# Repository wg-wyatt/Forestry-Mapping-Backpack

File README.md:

# Forestry Mapping Backpack

<table align="center" width="100%">
  <tr>
    <td align="center" valign="middle" width="50%">
      
      <br>
      <b>Exterior Assembly</b>
    </td>
    <td align="center" valign="middle" width="50%">
      
      <br>
      <b>Interior Assembly</b>
    </td>
  </tr>
</table>

---

## Overview
The LiDAR Backpack Mapping System is a mobile, human-wearable sensing platform engineered to improve 3D point cloud density and spatial coverage for forestry and ecological surveying. Developed to replace rigid mast-mounted sensors, the system integrates a continuous secondary rotation axis with onboard processing to optimize sensor range, lower the user's center of gravity, and improve ergonomics during extended field deployment.

---

## Key Features

- Rotating LiDAR platform
- Integrated IMU for spatial orientation
- Modular mechanical architecture
- MATLAB analysis supporting point cloud generation
- Timing belt-driven rotation system
- Custom KiCad PCB
- FEA-validated structural design
- Optimized for low-volume manufacturing

### Project Disclaimer

This project was completed in collaboration with the Purdue Forestry Department. Certain project details, files, and implementation documentation may be limited due to sponsor requirements and intellectual property considerations.

---

## Problem Statement
The Purdue Forestry Department utilizes a machine learning–based plant recognition system to assist researchers with ecological surveying and vegetation analysis. Their legacy setup relied on a static LiDAR sensor mounted atop a tall backpack support mast. This configuration suffered from two major limitations:
* **Limited Spatial Coverage:** The static sensor depended entirely on natural user motion during field traversal to expand scan coverage, leading to low point cloud density and occlusions.
* **Poor Ergonomics:** Positioning significant mass high above the backpack shifted the system's center of gravity, reducing stability and user comfort during extended hiking over uneven terrain.

The objective of this project was to engineer a field-deployable mounting platform that adds a continuous secondary rotation axis to maximize point cloud density while relocating system mass closer to the user's center of gravity.

---

## Design Requirements

The following design requirements were established during the concept development phase to guide system architecture and engineering decisions. Requirements were selected to balance field usability, sensing performance, manufacturability, and compatibility with the existing Purdue Forestry Department backpack platform.

### Mechanical Requirements

| ID | Requirement | Target | Verification Method |
|----|-------------|--------|---------------------|
| DR-01 | Total system weight | < 10 kg (excluding backpack) | CAD mass properties |
| DR-02 | Structural durability | Withstand 5 g loading without structural failure | Finite Element Analysis (FEA) |
| DR-03 | Manufacturability | Components shall be manufacturable using conventional CNC machining, sheet metal fabrication, additive manufacturing, and commercially available hardware | Design review and manufacturing drawings |
| DR-04 | Serviceability | Electronics and wearable components shall be removable without permanent modification to the assembly | Assembly review |

### Functional Requirements

| ID | Requirement | Target | Verification Method |
|----|-------------|--------|---------------------|
| FR-01 | Point cloud coverage | Provide 360° scanning with a secondary axis of rotation to improve spatial coverage and reduce occlusions | MATLAB analysis and future field validation |
| FR-02 | Rotational position tracking | Report motor position to ±0.01° for point cloud reconstruction | Encoder specification and software verification |

### Integration Requirements

| ID | Requirement | Target | Verification Method |
|----|-------------|--------|---------------------|
| IR-01 | Backpack compatibility | Integrate with the existing Purdue Forestry backpack frame, 24 V hot-swappable M18 battery system, and existing data interfaces | CAD integration and electrical design review |
| IR-02 | Environmental protection | Minimum enclosure protection equivalent to IP32 | Enclosure design review and future ingress testing |

---

## System Architecture

The LiDAR Backpack Mapping System is a modular mechatronic platform structured into four core subsystems: **Sensing**, **Motion Control**, **Power Distribution**, and **Processing & Data**. 

### Sensing System
The sensing subsystem consists of an Ouster OS1 LiDAR sensor paired with an Ellipse N inertial measurement unit (IMU). The LiDAR provides high-resolution 3D measurements, while the IMU provides time synchronization and spatial orientation. Combining these inputs with rotational position feedback enables full point-cloud reconstruction.

### Motion Control System
The motion control subsystem provides controlled rotation of the LiDAR assembly via a motor-driven mechanism. A geared timing belt transmission ensures stable torque delivery, while encoder feedback tracks rotational position to synchronize scanning motion with sensor data.

### Power Distribution System
The system utilizes a 24 V hot-swappable battery architecture inherited from the base backpack platform. Dedicated regulation hardware distributes power safely to the LiDAR, motor controller, embedded electronics, and compute unit.

### Processing and Data System
An NVIDIA Jetson Orin platform serves as the central compute unit, handling data acquisition, sensor synchronization, and point-cloud generation. Communication protocols across all hardware are streamlined to minimize external cabling and maintain reliable data transfer.

---

## Mechanical Design

<table border="0" cellpadding="10" cellspacing="0" width="100%">
  <tr>
    <td width="40%" align="center" valign="middle">
      
    </td>
    <td width="60%" valign="middle">
      <p>The mechanical architecture focuses on a modular, field-serviceable platform designed to integrate all sub-assemblies while maintaining full compatibility with the host Purdue Forestry backpack frame. The physical layout prioritizes low system mass, protected cable routing, and high structural rigidity under dynamic motion.</p>
    </td>
  </tr>
</table>

### Rotational Drive System
A motor-driven timing belt transmission provides continuous rotation for the LiDAR assembly based on velocity parameters defined in MATLAB. A compact T2 timing belt system was selected for high torque transfer and reliable engagement using off-the-shelf hardware.

The drivetrain uses a 15-tooth driving pulley and a 75-tooth driven pulley to deliver a 5:1 reduction ratio. This reduction increases output torque to provide smooth, stable rotational motion across variable operating speeds.

### Structural Packaging & Integration
The frame and enclosure assemblies are structured to support the mechanical loads of the continuous rotation drive without requiring structural overhaul of the base backpack:
* **Drive Support Frame:** Provides a rigid mounting interface for the motor, bearing stack, and pulley system to maintain precise belt alignment and tension during dynamic motion.
* **Unified Component Enclosure:** Houses the compute, power regulation, and data acquisition hardware within a single physical module, allowing for seamless electrical integration between the motion system and the original architecture
* **Serviceable Assemblies:** Component layouts allow the drive assembly or processing housing to be accessed and serviced independently without full frame disassembly.

---

## Electrical Design

The electrical architecture was designed to integrate the LiDAR sensor, IMU, motor control system, embedded controller, and onboard processing hardware into the existing Purdue Forestry backpack platform. The design focused on maintaining compatibility with the legacy 24 V power system while providing reliable communication between sensing, motion, and processing subsystems.

<p align="center">
  
  <br>
  <em>System Overview Diagram</em>
</p>

### Drive System

The purpose of the design is to provide closed-loop control of the LiDAR rotation axis while maintaining reliable communication between the motion hardware and the onboard processing system.

<p align="center">
  
  <br>
  <em>Motor Drive System Schematic</em>
</p>

The embedded controller communicates with the motor driver to provide rotational commands, including direction and speed control. The motor driver supplies the required power to the actuator while isolating the low-power control electronics from the higher-current motor circuit.

An encoder feedback system is integrated into the drive architecture to provide rotational position information. This feedback allows the system to monitor the actual motor position and provides the positional data required to synchronize the LiDAR scan with the mechanical rotation of the secondary axis.

The drive system architecture consists of:

- **Embedded controller:** Generates motion commands and manages communication with the motor driver and feedback devices.
- **Motor driver:** Converts low-power control signals into the required motor power output.
- **Motor and encoder:** Provide rotational actuation and position feedback for closed-loop monitoring.

The schematic was developed to separate power, control, and feedback signals, improving system organization and simplifying future troubleshooting, fabrication, and integration.

### PCB Design

A custom PCB was developed to consolidate system interfaces and simplify integration between the embedded controller, sensors, and external hardware. The board provides organized connections for power, communication, and control signals while reducing wiring complexity compared to a fully discrete implementation.

Future revisions would integrate additional functionality into a single consolidated interface board to further improve reliability, manufacturability, and ease of assembly.

<p align="center">
  
  <br>
  <em>Custom interface board routing and connector layout</em>
</p>

<p align="center">
  📂 <strong><a href="Electronics">View Schematic & Board Layout Files (Electronics Folder)</a></strong>
</p>

---

## System Software & Embedded Controls

The system utilizes an NVIDIA Jetson Orin Nano onboard compute module running custom proprietary software to process incoming sensor streams, generate real-time 3D point clouds, and execute plant species identification algorithms. Working in tandem with the primary compute, an embedded microcontroller manages closed-loop motor dynamics, sensor data acquisition, and precise timestamping:

* **Embedded Speed Control:** Interfaces directly with motor Hall effect sensors via the motor controller to provide closed-loop control. The motor operates at **35 Hz** to drive the geared transmission, maintaining the secondary axis LiDAR rotation at a continuous, stable **7 Hz**.
* **Encoder & IMU Data Processing:** Processes quadrature encoder data for real-time rotational position tracking while timestamping high-rate IMU telemetry to ensure precise spatial orientation and point cloud time synchronization.
* **Pipeline Processing:** Synchronizes raw LiDAR packet streams with orientation data, applying coordinate transformations and noise filtering to export uniform, high-density point cloud files (`.ply` / `.pcd`) ready for forestry canopy analysis.

📂 **[View Embedded System Firmware (Complete_Code.ino)](Analysis%20%26%20Code/Complete_Code/Complete_Code.ino)**

---

## LiDAR Coverage Analysis

Engineering analysis was used to establish design parameters and validate critical system decisions. The analysis process began by evaluating the relationship between LiDAR measurement characteristics and scanning motion, which informed the required rotational velocity of the system. Mechanical drive calculations were then performed to select an appropriate transmission design, followed by structural analysis of the final assembly.

### MATLAB Scanning Analysis
A MATLAB model was developed to simulate the point cloud generated by a LiDAR unit rotating about two independent axes. The objective of the analysis was to determine the external rotational frequency required to achieve complete and uniform point cloud coverage from a stationary position.

The LiDAR's internal emitter operates at a rotational frequency of 10 Hz. Because the LiDAR was mounted on a secondary rotating axis, the relationship between the internal scan frequency and the external rotational frequency directly influences point cloud density and spatial coverage. Selecting an external rotational frequency that is an integer factor or multiple of the internal 10 Hz scan frequency results in periodic overlap of the scan pattern, producing incomplete coverage and gaps within the reconstructed point cloud.

Multiple external rotational frequencies were evaluated using the MATLAB model. Simulation results demonstrated that secondary axis rotational frequencies of **3 Hz** and **7 Hz** produced the most uniform point cloud distribution while minimizing repeated scan paths. Based on these results, the external rotational speed requirement for the mechanical drive system was established.

<p align="center">
  
  <br>
  <em>MATLAB Simulation showing point cloud coverage density over a 360-degree sweep at a 2.0 RPM target secondary axis speed</em>
</p>

The complete simulation script used to model the scanning spatial density can be accessed here:
👉 **[LiDAR_CoverageArea.m](Analysis%20%26%20Code/LiDAR_CoverageArea.m)**

### Rotation System and Gear Design

The rotational drive system was developed to achieve the operating speed established through the MATLAB analysis while maintaining reliable torque transmission and compact packaging.

A T2 timing belt was selected to provide positive, slip-free torque transmission between the motor and the rotating LiDAR assembly. Manufacturer design recommendations from MiSUMi were used during transmission selection, including a maximum recommended reduction ratio of **5:1** and a minimum pinion tooth engagement greater than six teeth. A 2 mm pitch timing belt was selected because it is commonly used in high-precision, low-speed motion systems and is readily available as a commercial component.

Using the selected pinion gear, the driven pulley diameter, tooth count, center-to-center pulley spacing, and timing belt length were analytically determined to satisfy both the required reduction ratio and packaging constraints.

Once the drivetrain geometry was established, the rotating assembly was modeled to estimate its mass moment of inertia. The driven pulley was approximated as a solid cylinder, while the LiDAR assembly was modeled as a rotating mass about the same axis. These values were used to calculate the torque required to accelerate the system to its operating speed within the desired startup time.

The calculated rotational speed and torque requirements were compared against the selected motor specifications to verify that the drivetrain would operate within the manufacturer's recommended operating range.

<p align="center">
  📂 <strong><a href="Analysis%20%26%20Code/GearSystemCalc.pdf">View Gear System Calculations (GearSystemCalc.docx)</a></strong>
</p>

## Structural & Dynamic Analysis (FEA)

Finite element analysis (FEA) was performed to evaluate the structural integrity and dynamic response of the redesigned LiDAR backpack assembly under operational shock and vibration conditions. 

<p align="center">
  
  <br>
  <em>Full Assembly Static Stress Distribution (5 g Inertial Shock Load)</em>
</p>

### Static Structural Analysis
A uniform **5 g inertial shock acceleration** was applied to evaluate structural yield margins during field transport. Component materials were modeled as linear elastic, with sheet metal structures utilizing shell or solid elements based on section thickness. Non-structural electronics were represented as equivalent point masses to maintain accurate inertial loading while optimizing solver performance.

<div align="center">

| Assembly / Component | Max Displacement | Max Von Mises Stress | Factor of Safety (FoS) |
| :--- | :---: | :---: | :---: |
| **LiDAR Mounting Bracket** | 0.044 mm | 13.42 MPa | 20.62 |
| **Motor Bracket Assembly** | 0.048 mm | 13.00 MPa | 4.95 |
| **Full Structural Assembly** | 0.085 mm | 15.30 MPa | 4.27 |

</div>

* **Structural Integrity:** The carbon fiber backplate and aluminum mounting hardware maintain significant structural margin under 5 g shock conditions, exceeding yield safety factor requirements with a minimum assembly FoS of **4.27x**.
* **Deflection Limits:** Maximum full-assembly displacement is constrained to **0.085 mm**, maintaining precise positional stability for high-accuracy point cloud generation.

---

### Modal Frequency Analysis
Modal analysis was performed to identify assembly natural frequencies and prevent forced resonance with primary system excitation sources (LiDAR internal sweep at 10 Hz, secondary axis at 7 Hz, and drive motor rotation at 35 Hz).

<p align="center">
  
  <br>
  <em>Primary Assembly Mode Shape (3.77 Hz Fundamental Frequency)</em>
</p>

<div align="center">

| Mode | Natural Frequency (Hz) | Dynamic Mode Behavior |
| :---: | :---: | :--- |
| **1** | 3.77 Hz | Global oscillation of LiDAR assembly relative to backplate |
| **2** | 4.77 Hz | Torsional and lateral assembly deflection |
| **3** | 11.52 Hz | Secondary structural bending mode |
| **4** | 72.41 Hz | High-frequency backplate bending |
| **5** | 80.81 Hz | Localized bracket structural mode |

</div>

* **Resonance Avoidance:** System modal frequencies successfully clear the primary operating frequencies of the rotating LiDAR (10 Hz) and drive motor (35 Hz), significantly reducing the risk of operational resonance during scanning.
* **Global Dynamic Behavior:** While the fundamental natural frequency (3.77 Hz) lies near human walking cadence (1.5–2.5 Hz and harmonics), localized stiffening modifications (such as motor bracket gussets) produced minimal frequency shifts. This demonstrates that strain energy is distributed globally across the structure, with overall dynamic behavior governed by global mass distribution and system geometry rather than local stiffness.*

---

## Design for Manufacturing

The LiDAR Backpack Mapping System was designed with low-volume fabrication in mind. While the system was developed as a research prototype, the mechanical architecture prioritized manufacturability, accessibility of components, and ease of assembly using processes available to small-scale fabrication shops.

### Manufacturing Approach

The design utilizes a combination of conventional manufacturing methods, including CNC machining, sheet metal fabrication, additive manufacturing, and commercially available hardware. Manufacturing processes were selected based on part function, required precision, and cost considerations.

Critical structural and alignment features were designed around machinable interfaces, while non-critical components were designed to reduce manufacturing complexity and allow rapid iteration.

### Component Selection

Commercially available components were incorporated where possible to reduce custom fabrication requirements. Examples include:

- Timing belt and pulley components
- Bearings
- Fasteners
- Motor and encoder hardware
- Electrical connectors

Using standardized components reduces lead times, simplifies replacement, and improves long-term serviceability.

### Assembly and Serviceability

The system was designed as a modular assembly with separate mechanical, electrical, and sensing components. This approach allows individual subsystems to be accessed, replaced, or modified without requiring complete disassembly of the platform.

Design considerations included:

- Accessible fasteners
- Modular enclosure design
- Cable routing considerations
- Separation of structural and electronic components

### Future Manufacturing Considerations

If transitioned from prototype design to production, additional engineering documentation would be developed, including detailed manufacturing drawings, tolerance specifications, and GD&T on critical interfaces.

Potential future manufacturing validation would include:

- Fabrication of prototype components
- Assembly verification
- Dimensional inspection
- Structural testing

---

## Project Status

The LiDAR Backpack Mapping System was developed as part of a senior design project in collaboration with the Purdue Forestry Department. The project progressed through multiple design iterations, beginning with the development of a benchmark system and continuing toward a fully integrated field-deployable platform.

### Benchmark System

An initial benchmark system was developed by the senior design team to provide a functional platform for evaluating the plant recognition workflow. This system utilized lower-grade electronics and a simplified mounting approach that allowed it to be installed on the existing backpack platform.

The benchmark system established a baseline hardware configuration and provided a foundation for future development. Further validation of the benchmark system with the plant recognition algorithm is planned.

### Integrated System Design

The current iteration focuses on integrating the complete sensing, motion, power, and processing architecture into a single manufacturable platform. The detailed design phase has been completed, including:

- Mechanical system design
- Sensor and hardware integration
- Electrical architecture development
- Motion system analysis
- MATLAB-based scanning analysis
- Manufacturing considerations

The system is currently at the fabrication-ready stage. Fabrication and physical validation will proceed upon sponsor approval and project continuation.

---

## Future Work

The next phase of development would focus on fabrication, system integration, and validation of the completed design. Future work would transition the system from a fabrication-ready design into a fully tested field deployment platform.

### Prototype Fabrication and Integration

Future work would begin with fabrication and assembly of the redesigned LiDAR platform. This phase would include the integration of the mechanical assembly, electrical hardware, sensing components, and onboard processing system.

Planned integration tasks include:

- Fabrication of mechanical components
- Assembly of the rotating LiDAR mechanism
- Integration of sensors, motor controller, and electronics
- Verification of mechanical and electrical interfaces

#### Mechanical Validation

Testing would include:

- **Weight validation:** Confirm total system mass meets the design requirement.
- **Drop testing:** Evaluate structural durability and ensure components remain functional after accidental impacts.
- **Backpack mobility testing:** Evaluate system usability during normal hiking conditions and verify that the updated mounting configuration improves integration with the backpack platform.

#### Environmental Validation

The enclosure and hardware protection would be evaluated through:

- Weather exposure testing
- Verification of enclosure protection against environmental conditions
- Confirmation that internal electronics remain protected during field operation

#### Data Collection and Algorithm Validation

The sensing system would be evaluated through field data collection tests, including:

- **Wall test:** Walking the backpack along a controlled surface to evaluate point cloud consistency and rotational accuracy.
- Validation of LiDAR point cloud generation with the plant recognition algorithm.
- Evaluation of sensor synchronization and positional tracking accuracy.

#### Electrical Validation

Electrical integration testing would verify:

- Stable power delivery from the existing 24 V battery system
- Reliable communication between sensors, motor controller, and processing hardware
- Continuous operation of the motor and sensing systems during data collection

### Future Hardware Improvements

Additional hardware improvements identified during the design process include:

- Replacing the Arduino Nano-based control system with an STM32 microcontroller to improve processing capability, communication flexibility, and future expandability.
- Consolidating the current distributed PCB architecture into a single integrated interface board to reduce wiring complexity, improve reliability, and simplify assembly.

---

## Skills Demonstrated

### Mechanical Design
- SolidWorks CAD modeling and assembly design
- Mechanical packaging and system integration
- Timing belt transmission design and gear ratio calculations
- Structural design considerations for field-deployed hardware
- Design for manufacturing (CNC machining, sheet metal fabrication, additive manufacturing)
- Modular assembly and serviceability considerations

### Electrical and Embedded Systems
- System-level electrical architecture development
- Power distribution and hardware integration
- Sensor and actuator interfacing
- PCB system design using KiCad
- Embedded controller integration and communication planning

### Engineering Analysis
- MATLAB-based system modeling and scanning analysis
- Rotational velocity optimization
- Mechanical drivetrain calculations
- Torque and load analysis
- Finite Element Analysis 

### Engineering Tools
- SolidWorks
- KiCad
- MATLAB
- Python
- Technical documentation
  
---

## Acknowledgments

This project was completed in collaboration with the Purdue Forestry Department as part of a senior design project focused on improving field deployment of plant recognition and LiDAR mapping systems.

Special thanks to **Evan Flatt, Purdue Forestry Department**, for sponsoring the project, providing the application requirements, domain knowledge, and guidance that informed the system design.

The initial benchmark platform was developed from an existing legacy system and served as the foundation for subsequent design iterations. The integrated LiDAR mapping platform presented in this portfolio represents the continued development of that system, including the mechanical redesign, system architecture, drivetrain analysis, and integration planning.

Additional contributions from team members are acknowledged where applicable, including assistance with software development and specific CAD contributions.

---

## References

<blockquote>
  <p align="center">
    <strong>📚 Academic & Technical References coming soon.</strong><br>
    Currently compiling literature on LiDAR spatial mapping algorithms, 2D-to-3D point cloud reconstruction math, and academic papers on forestry canopy density measurement standards.
  </p>
</blockquote>

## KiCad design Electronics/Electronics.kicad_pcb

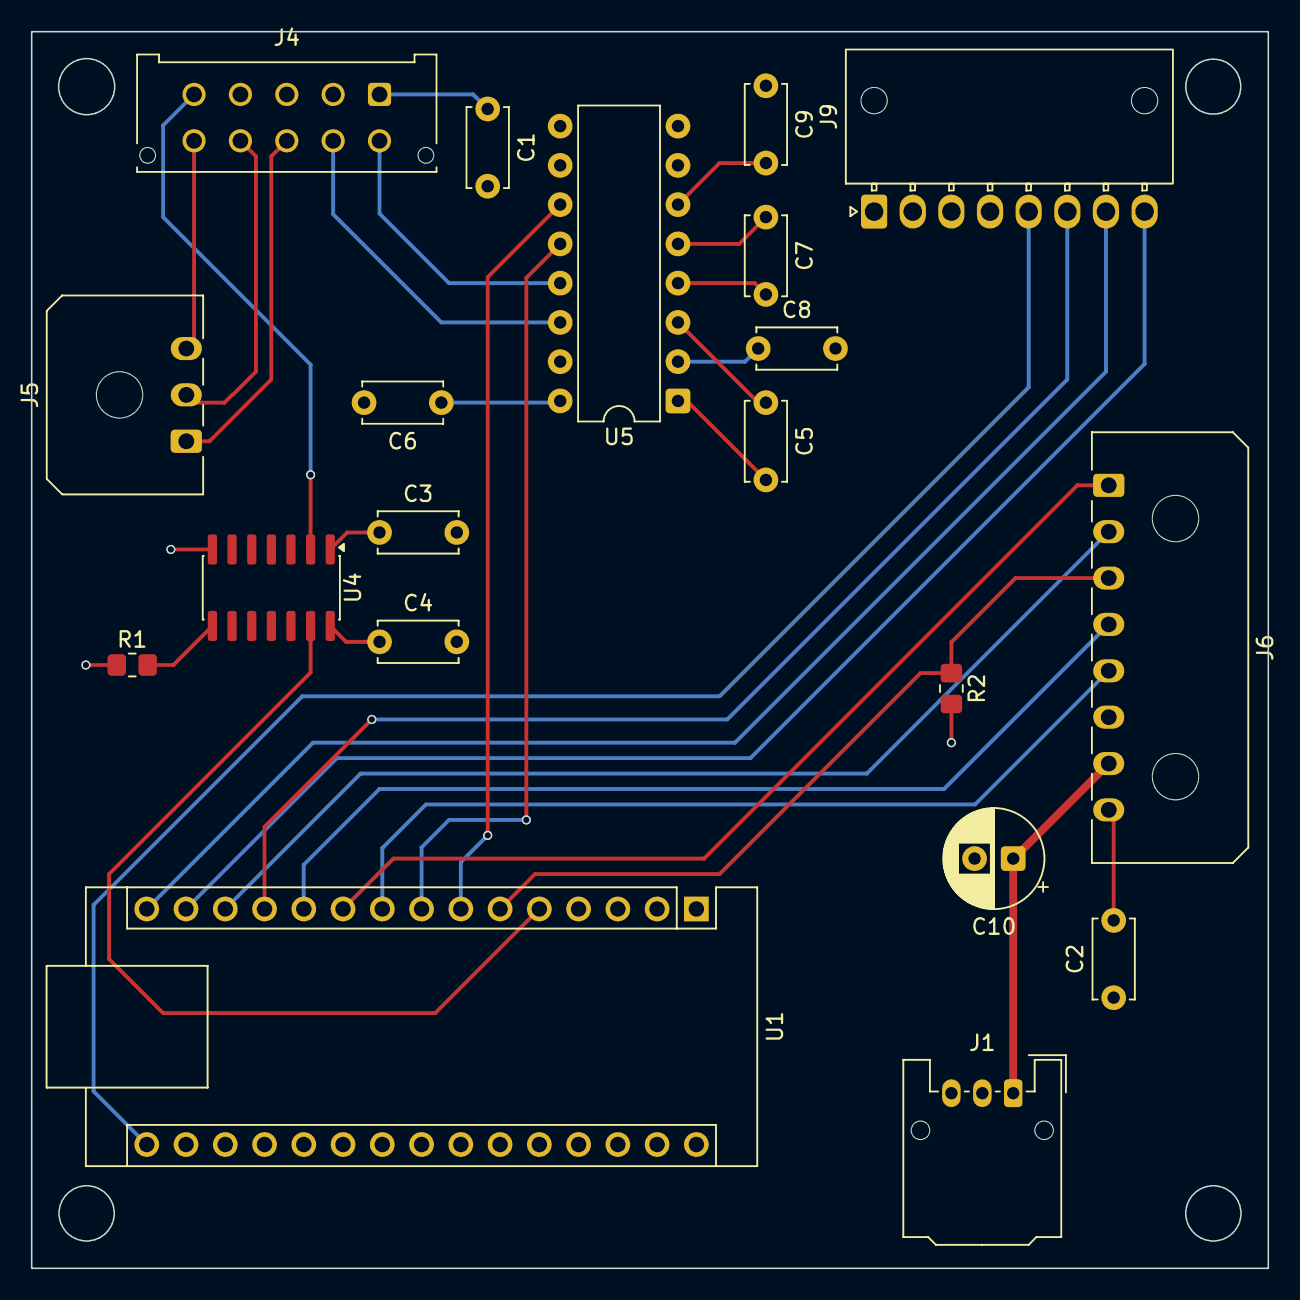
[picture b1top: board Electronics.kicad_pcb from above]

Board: 6 copper layers, 80.0 x 80.0 mm, 20 parts (0 on the bottom side), 29 nets.

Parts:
C1, C2, C3, C4, C5, C6, C7, C8, C9: 0.1uF; C_Disc_D5.0mm_W2.5mm_P5.00mm
C10: 100uF; CP_Radial_D6.3mm_P2.50mm
J1: MDS_PWR_IN; Molex_MicroClasp_55935-0310_1x03_P2.00mm_Horizontal
J4: IMU_EllipseN; Molex_Micro-Fit_3.0_43045-1012_2x05_P3.00mm_Vertical
J5: IMU_TO_PropPCB; Molex_Micro-Fit_3.0_43650-0300_1x03_P3.00mm_Horizontal
J6: MTR_CTR_CONN; Molex_Micro-Fit_3.0_43650-0800_1x08_P3.00mm_Horizontal
J9: Magnetic Encoder Connector; Molex_Nano-Fit_105313-xx08_1x08_P2.50mm_Horizontal
R1: 10kO; R_0805_2012Metric_Pad1.20x1.40mm_HandSolder
R2: 22kO; R_0805_2012Metric_Pad1.20x1.40mm_HandSolder
U1: Arduino_Nano_v2.x; Arduino_Nano
U4: TXS0104ED; SOIC-14_3.9x8.7mm_P1.27mm
U5: MAX3232; DIP-16_W7.62mm

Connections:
+3.3V: C1.1, C3.1, J4.3 (Vin), R1.1, R2.2, U1.17 (3V3), U4.1 (V_{CCA})
+5V: C2.2, C4.1, C6.1, C8.2, J1.3, J6.8, J9.1 (5V), U1.27 (+5V), U4.14 (V_{CCB}), U5.16 (VCC)
+24V: C10.1, J1.1, J6.7
/IMU_RS422_RX: J4.10 (Port_B_RX), J5.3 (Port_E_RX)
/IMU_RS422_TX: J4.7 (Port_B_TX), J5.2 (Port_E_TX)
/IMU_SYNC_B: J4.2 (Sync_in_B), J5.1 (Sync_in_B)
/MOT_ENBL: J6.1, U1.10 (D7)
/MOT_FAULT: J6.3, R2.1, U1.6 (D3)
/MOT_PWM: J6.5, U1.9 (D6)
/MOT_ROT_DIR: J6.4, U1.11 (D8)
/MOT_RUN: J6.2, U1.13 (D10)
/MotorDriveSystem/ENC_MISO: J9.7 (MISO_TX+), U1.15 (D12)
/MotorDriveSystem/ENC_MOSI: J9.8 (MOSI_TX-), U1.14 (D11)
/MotorDriveSystem/ENC_NCS: J9.6 (NCS_RX-), U1.12 (D9)
/MotorDriveSystem/ENC_SCK: J9.5 (SCK_RX+), U1.16 (D13)
/MotorDriveSystem/IMU_SYNC_IN: U1.5 (D2), U4.13 (B1)
/MotorDriveSystem/IMU_SYNC_OUT: J4.6 (Sync_OUT), U4.2 (A1)
/MotorDriveSystem/NANO_RS232_RX: J4.8 (Port_A_TX), U5.13 (R1IN)
/MotorDriveSystem/NANO_RS232_TX: J4.9 (Port_A_RX), U5.14 (T1OUT)
/MotorDriveSystem/NANO_UART_RX: U1.8 (D5), U5.12 (R1OUT)
/MotorDriveSystem/NANO_UART_TX: U1.7 (D4), U5.11 (T1IN)
GND: C1.2, C2.1, C3.2, C4.2, C6.2, C9.1, C10.2, J1.2, J4.4 (GND), J6.6, J9.2 (GND), U1.4 (GND), U1.29 (GND), U4.7 (GND), U5.15 (GND)
unnamed: R1.2, U4.8 (OE)
unnamed: C5.2, U5.1 (C1+)
unnamed: C5.1, U5.3 (C1-)
unnamed: C7.2, U5.4 (C2+)
unnamed: C7.1, U5.5 (C2-)
unnamed: C8.1, U5.2 (VS+)
unnamed: C9.2, U5.6 (VS-)

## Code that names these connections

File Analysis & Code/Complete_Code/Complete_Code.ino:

/**
 * @file main.cpp
 * @brief Motor Drive & IMU Synchronization System
 * 
 * @author Stefan Vin
 * @generated_with Gemini
 * @date 2026-07-23
 */
 
#include <TinyGPS++.h>
#include <SoftwareSerial.h>
#include <SPI.h>

// --- SCHEMATIC PIN DEFINITIONS ---
#define IMU_SYNC_PIN 2   // D2 - IMU_SYNC_IN (PPS / Time Sync Input)
#define MOT_FAULT_PIN 3  // D3 - MOT_FAULT (Input from Motor Controller)
#define IMU_RX_PIN    5  // D5 - NANO_UART_RX (From MAX3232 R1OUT)
#define IMU_TX_PIN    4  // D4 - NANO_UART_TX (To MAX3232 T1IN)
#define MOT_PWM_PIN   6  // D6 - MOT_PWM (Speed Control)
#define MOT_ENBL_PIN  7  // D7 - MOT_ENBL (Driver Enable)
#define MOT_DIR_PIN   8  // D8 - MOT_ROT_DIR (Rotation Direction)
#define ENC_CS_PIN    9  // D9 - ENC_NCS (AksIM-2 SPI Chip Select)
#define MOT_RUN_PIN   10 // D10 - MOT_RUN (Run/Stop Line)

// Hardware SPI Pins on Arduino Nano:
// D11 = MOSI, D12 = MISO, D13 = SCK

// --- SETTINGS ---
const int targetMotorSpeed = 51; // Constant PWM speed (0-255)

// --- OBJECTS & VARIABLES ---
TinyGPSPlus gps;
SoftwareSerial imuSerial(IMU_RX_PIN, IMU_TX_PIN); // RX = Pin 5, TX = Pin 4

volatile unsigned long lastPPSMillis = 0;
volatile bool ppsTriggered = false;

unsigned long lastEncoderMillis = 0;
bool motorRunning = true;

// ISR for PPS Interrupt on D2
void ppsHandler() {
    lastPPSMillis = millis();
    ppsTriggered = true;
}

void setup() {
    // Standard Hardware Serial for Debugging / Commands
    Serial.begin(115200);
    
    // Software Serial for IMU Communication (via MAX3232)
    imuSerial.begin(9600);
    
    // PPS Interrupt Setup
    pinMode(IMU_SYNC_PIN, INPUT);
    attachInterrupt(digitalPinToInterrupt(IMU_SYNC_PIN), ppsHandler, FALLING);

    // Encoder SPI Setup
    pinMode(ENC_CS_PIN, OUTPUT);
    digitalWrite(ENC_CS_PIN, HIGH);
    SPI.begin();

    // Motor Controller Pins Setup
    pinMode(MOT_PWM_PIN, OUTPUT);
    pinMode(MOT_ENBL_PIN, OUTPUT);
    pinMode(MOT_DIR_PIN, OUTPUT);
    pinMode(MOT_RUN_PIN, OUTPUT);
    pinMode(MOT_FAULT_PIN, INPUT);

    // Initial Motor State Setup
    digitalWrite(MOT_DIR_PIN, LOW);   // Set default direction
    digitalWrite(MOT_ENBL_PIN, HIGH); // Enable controller bridge
    digitalWrite(MOT_RUN_PIN, HIGH);  // Set Run active
    analogWrite(MOT_PWM_PIN, targetMotorSpeed);
    
    Serial.println(F("System Initialized. Commands: 'stop', 'go'."));
}

uint32_t readEncoder() {
    SPI.beginTransaction(SPISettings(4000000, MSBFIRST, SPI_MODE0));
    digitalWrite(ENC_CS_PIN, LOW);
    
    uint32_t b1 = SPI.transfer(0x00);
    uint32_t b2 = SPI.transfer(0x00);
    uint32_t b3 = SPI.transfer(0x00);
    
    digitalWrite(ENC_CS_PIN, HIGH);
    SPI.endTransaction();

    return (b1 << 16) | (b2 << 8) | b3;
}

void printfTime(int h, int m, int s, unsigned long ms) {
    if (ms > 999) ms = 999;
    char buf[25];
    sprintf(buf, "%02d:%02d:%02d.%03lu", h, m, s, ms);
    Serial.println(buf);
}

void loop() {
    // 1. Process Serial Data from IMU
    while (imuSerial.available() > 0) {
        gps.encode(imuSerial.read());
    }

    // 2. Handle PPS Event Flag Safely
    if (ppsTriggered) {
        ppsTriggered = false;
        Serial.println(F("[SYNC] PPS Edge Detected"));
    }

    // 3. Serial Command Processing
    if (Serial.available()) {
        String cmd = Serial.readStringUntil('\n');
        cmd.trim();
        
        if (cmd.equalsIgnoreCase("stop")) {
            motorRunning = false;
            digitalWrite(MOT_RUN_PIN, LOW);   // Disable output drive
            analogWrite(MOT_PWM_PIN, 0);
            Serial.println(F(">>> MOTOR STOPPED"));
        } 
        else if (cmd.equalsIgnoreCase("go")) {
            motorRunning = true;
            digitalWrite(MOT_RUN_PIN, HIGH);  // Resume output drive
            analogWrite(MOT_PWM_PIN, targetMotorSpeed);
            Serial.println(F(">>> MOTOR RESUMED"));
        }
    }

    // 4. Check for Motor Controller Faults
    if (digitalRead(MOT_FAULT_PIN) == HIGH) {
        // Adjust polarity based on Faulhaber SC2804S fault pin logic (active HIGH/LOW)
        // Serial.println(F("WARNING: Motor Controller Fault Pin Triggered!"));
    }

    // 5. 100Hz Logging Loop (10ms interval)
    if (millis() - lastEncoderMillis >= 10) {
        lastEncoderMillis = millis();
        
        uint32_t rawEncoder = readEncoder();
        unsigned long offset = millis() - lastPPSMillis;
        
        Serial.print(F("ENC: "));
        Serial.print(rawEncoder);
        Serial.print(F(" | UTC: "));
        
        if (gps.time.age() < 2000 && gps.time.isValid()) { 
            printfTime(gps.time.hour(), gps.time.minute(), gps.time.second(), offset);
        } else {
            Serial.println(F("NO TIMING DATA"));
        }
    }
}
